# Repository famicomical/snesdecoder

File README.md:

# SNES Controller Decoder #
It's a receiver for Super Nintendo Controllers.

I use it to drive the button inputs on the IS-NITRO CAPTURE dev console.
With some soldering skills, one could adapt it for any application where up
to twelve switches need to be controlled from a distance. For example, you can use the snesdecoder 
to play your Neo Geo console or JAMMA arcade game with your SNES controller.

## Design Sketch ##
The SNES controller takes 4 inputs (GND, 5V, CLK, and LATCH) and sends one serial output for button press data.
This board routes power to the controller and provides the clock & latch signals to drive it.
The button data from the controller is sent back to the decoder pcb, which outputs the buttons in parallel.

The clock is generated using a ring oscillator whose period is set by an external RC time constant. See [Fairchild AN-118](https://www.onsemi.com/pub/Collateral/AN-118.pdf.pdf). 
The ripple carry output of a 4-bit counter supplies the latch signal. This way, the SNES controller is polled every 16 clock cycles, which is enough time to transmit a full data packet. The counter also drives the register clock on the shift register(s), thereby updating the open drain outputs to reflect the button data of the preceding packet until the next packet is received.

To produce a working board, some quirks were taken into account:

The SNES button data is logic high when a button is NOT pressed, so the data stream needs to be inverted before going to the shift register(s) for canonical switch behavior, i.e. not pressed -> open circuit. Also, the latch and clock outputs going to the controller need dedicated buffers, otherwise the interference between the wires in the controller cable feeds back to the decoder board, causing malfunctions. Lastly, the clock signal being fed to the shift register(s) should be inverted so the button states are sampled from the data stream roughly at the midpoint of each button's time-bin.

Detailed info about the SNES contoller can be found on [GameSX](https://gamesx.com/controldata/snesdat.htm)

## Motivation ##
This project was inspired by an [old forum post](https://nfggames.com/forum2/index.php?msg=26296) on NFGgames.

I wanted to use my SNES controller on other consoles, but I felt a universal computer would be 
overkill for accomplishing that. All of the existing solutions that I'm aware of use a computer or custom logic. 
With discrete components that don't require programming, this design is trasparent about what it does, and is
reminiscent of the simpler times when transistors were more expensive and packaging less so by comparison :P

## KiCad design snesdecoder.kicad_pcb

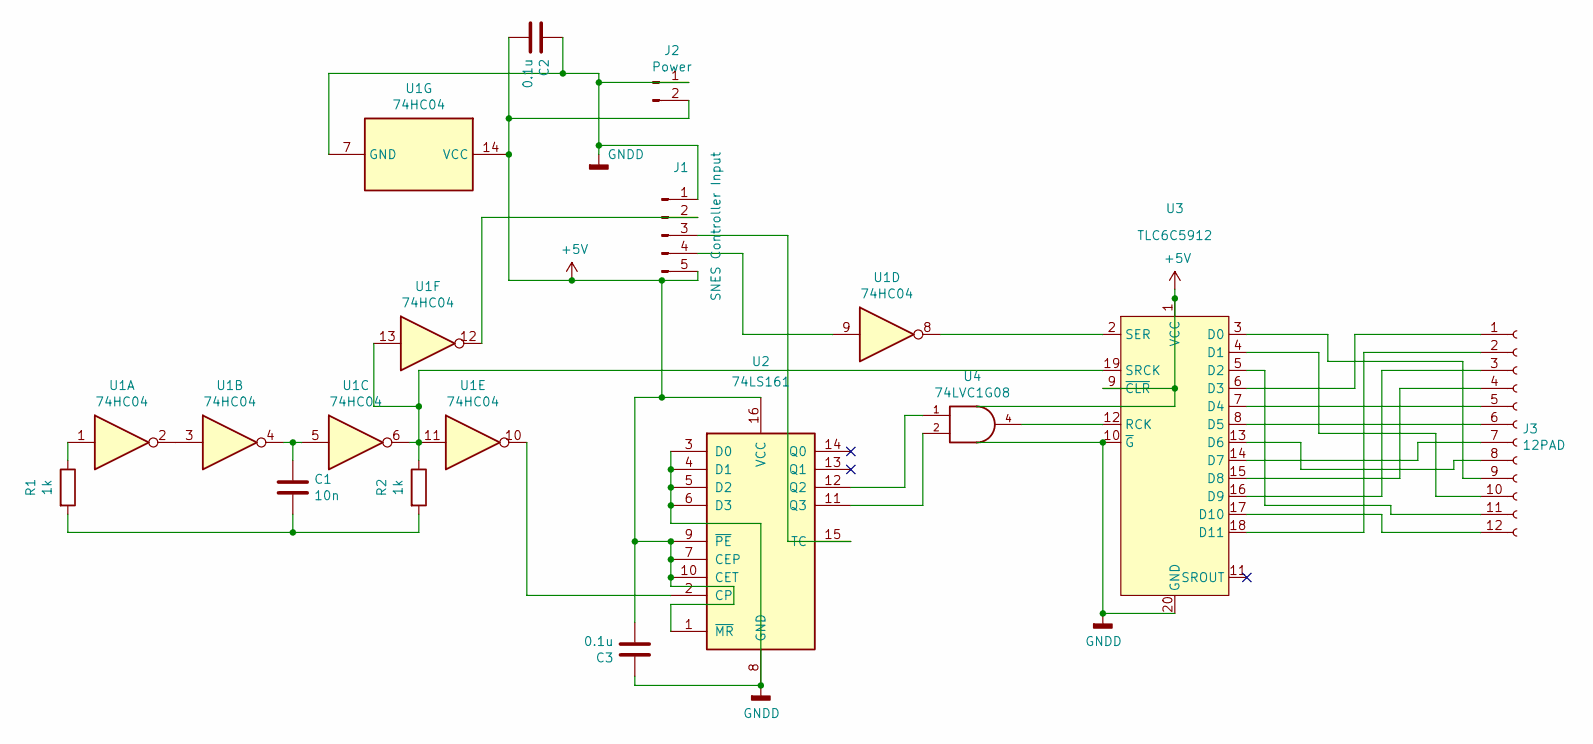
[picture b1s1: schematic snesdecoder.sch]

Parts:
C1: 10n; C_0805_2012Metric_Pad1.15x1.40mm_HandSolder
C2, C3: 0.1u; C_0805_2012Metric_Pad1.15x1.40mm_HandSolder
J1: SNES Controller Input; Connector_Wire_5PAD
J2: Power; 2PAD_Pwrr
J3: 12PAD
R1, R2: 1k; R_0805_2012Metric_Pad1.15x1.40mm_HandSolder
U1: 74HC04; SOIC-14_3.9x8.7mm_P1.27mm
U2: 74LS161; SOIC-16_3.9x9.9mm_P1.27mm
U3: TLC6C5912; SOIC-20W_7.5x12.8mm_P1.27mm
U4: 74LVC1G08; SOT-353_SC-70-5_Handsoldering

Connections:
+5V: C2.2, C3.2, J1.5, J2.2, U1.14 (VCC), U2.1 (~MR), U2.7 (CEP), U2.9 (~PE), U2.10 (CET), U2.16 (VCC), U3.1 (VCC), U3.9 (~CLR), U4.5 (VCC)
GND: C2.1, C3.1, J1.1, J2.1, U1.7 (GND), U2.3 (D0), U2.4 (D1), U2.5 (D2), U2.6 (D3), U2.8 (GND), U3.10 (~G), U3.20 (GND), U4.3 (GND)
unnamed: C1.1, U1.4, U1.5
unnamed: C1.2, R1.2, R2.2
unnamed: J1.2, U1.12
unnamed: J1.3, U2.15 (TC)
unnamed: J1.4, U1.9
unnamed: J3.1, U3.6 (D3)
unnamed: J3.2, U3.18 (D11)
unnamed: J3.3, U3.16 (D9)
unnamed: J3.4, U3.15 (D8)
unnamed: J3.5, U3.7 (D4)
unnamed: J3.6, U3.8 (D5)
unnamed: J3.7, U3.14 (D7)
unnamed: J3.8, U3.13 (D6)
unnamed: J3.9, U3.3 (D0)
unnamed: J3.10, U3.4 (D1)
unnamed: J3.11, U3.5 (D2)
unnamed: J3.12, U3.17 (D10)
unnamed: R1.1, U1.1
unnamed: R2.1, U1.6, U1.11, U1.13, U3.19 (SRCK)
unnamed: U1.2, U1.3
unnamed: U1.8, U3.2 (SER)
unnamed: U1.10, U2.2 (CP)
unnamed: U2.11 (Q3), U4.2
unnamed: U2.12 (Q2), U4.1
unnamed: U3.12 (RCK), U4.4

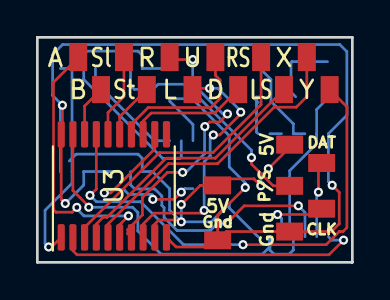
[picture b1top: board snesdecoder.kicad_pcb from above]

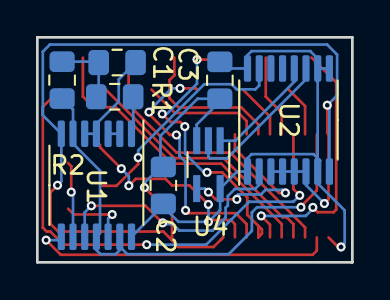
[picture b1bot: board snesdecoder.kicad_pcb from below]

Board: 2 copper layers, 17.5 x 12.5 mm, 12 parts (8 on the bottom side), 27 nets.

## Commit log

2020-11-09 Initial commit: Snes Decoder V1 ready
2020-11-09 updated gerbers
2020-11-09 update gerbers
2020-11-09 remove old files
2020-11-09 add graphic for readme
2020-11-15 update to V2: change schema, pcb layout, datasheets
2020-11-15 update datasheets
2020-11-15 gerbers to v2
2020-11-20 snesdecoder compact release
2020-11-20 fix sch
2023-03-16 add figures
